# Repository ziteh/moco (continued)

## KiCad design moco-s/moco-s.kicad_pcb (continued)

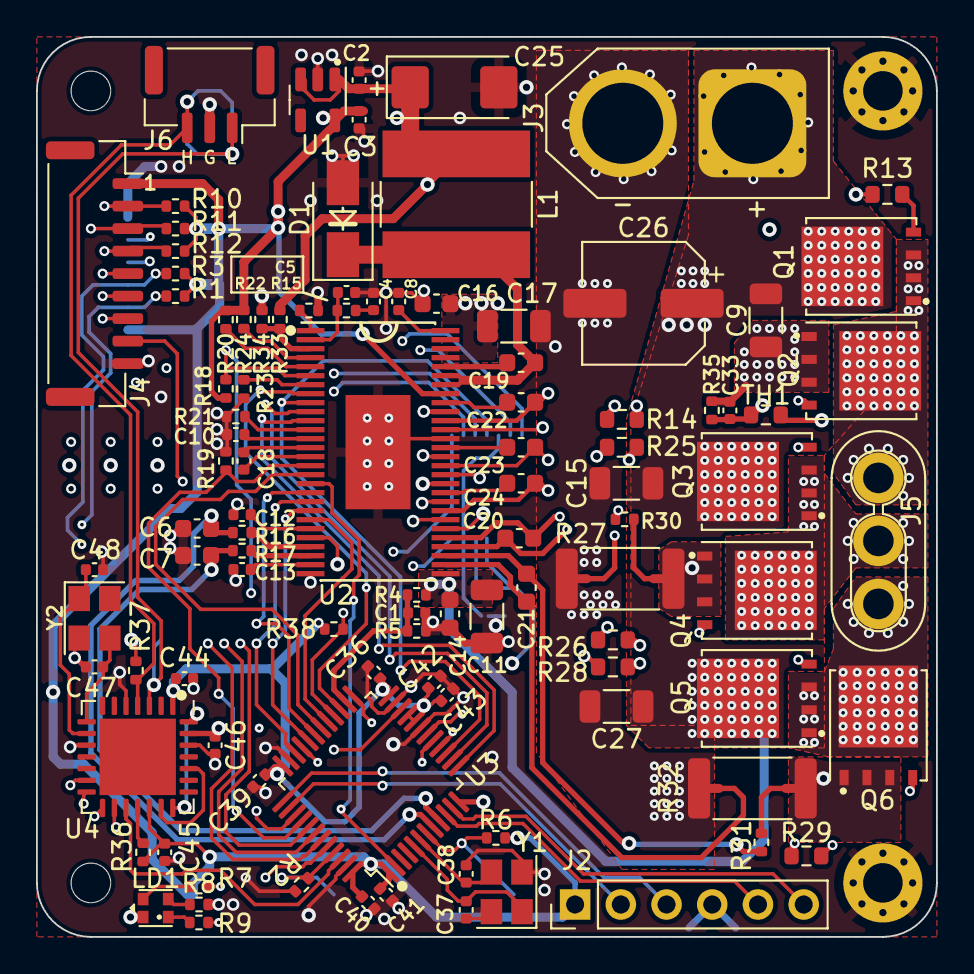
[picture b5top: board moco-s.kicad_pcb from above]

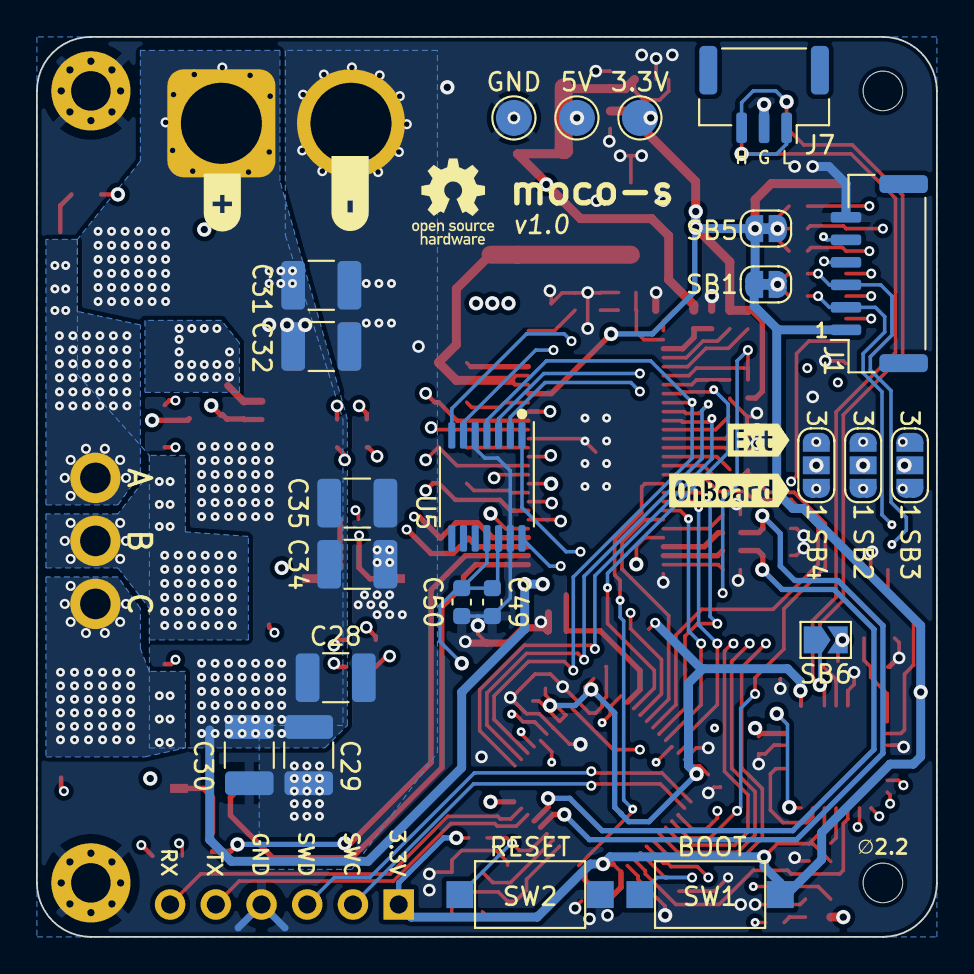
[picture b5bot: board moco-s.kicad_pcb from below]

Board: 4 copper layers, 50.0 x 50.0 mm, 135 parts (27 on the bottom side), 103 nets.

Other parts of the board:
J5: Conn_01x03; AMASS MR30PB-F
kibuzzard-638C8B7C: G***; kibuzzard-638C8B7C
kibuzzard-638C8BCF: G***; kibuzzard-638C8BCF
kibuzzard-638C8E4D: G***; kibuzzard-638C8E4D
kibuzzard-638C8E29: G***; kibuzzard-638C8E29

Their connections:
/Motor Driver/MOTOR_A: J5.1; also elsewhere on the board
/Motor Driver/MOTOR_B: J5.2; also elsewhere on the board
/Motor Driver/MOTOR_C: J5.3; also elsewhere on the board

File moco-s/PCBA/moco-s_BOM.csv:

Comment,Designator,Footprint,LCSC
82pF,C5,C_0402_1005Metric,C107011
47uF/50V,C26,CP_Elec_6.3x7.7,C108053
15nF,C8,C_0402_1005Metric,C114405
1k,"R19,R8",R_0402_1005Metric,C11702
NCP18XH103F03RB,TH1,R_0603_1608Metric,C13564
16MHz,Y2,Crystal_SMD_3225-4Pin_3.2x2.5mm,C13738
100nF/50V,"C14,C16,C19,C22,C23,C24",C_0603_1608Metric,C14663
100nF,"C36,C39,C40,C41,C42,C44,C45,C46",C_0402_1005Metric,C1525
22nF,C18,C_0402_1005Metric,C1532
12pF,"C37,C38",C_0402_1005Metric,C1547
10uF,C2,C_0402_1005Metric,C15525
22pF,"C47,C48",C_0402_1005Metric,C1555
2.2nF,"C20,C21,C6,C7",C_0603_1608Metric,C1604
MCP25625,U4,QFN-28-1EP_6x6mm_P0.65mm_EP4.25x4.25mm,C191253
2.2R,"R13,R14,R25,R26,R28,R29",R_0603_1608Metric,C22939
4.7uF,C3,C_0402_1005Metric,C23733
120R,"R30,R31,R37",R_0402_1005Metric,C25079
22R,"R16,R17",R_0402_1005Metric,C25092
330R,R9,R_0402_1005Metric,C25104
680R,"R5,R7",R_0402_1005Metric,C25130
10k,"R18,R2,R20,R24,R35,R36,R38,R4,R6",R_0402_1005Metric,C25744
18k,"R23,R33",R_0402_1005Metric,C25762
220k 1%,R22,R_0402_1005Metric,C25767
47k,R15,R_0402_1005Metric,C25792
3.3k,"R10,R11,R12,R21,R34",R_0402_1005Metric,C25890
4.7k,"R1,R3",R_0402_1005Metric,C25900
Conn_02x02_Top_Bottom,"J6,J7",JST_GH_SM03B-GHS-TB_1x03-1MP_P1.25mm_Horizontal,C2829252
Conn_01x06,J1,JST_GH_SM06B-GHS-TB_1x06-1MP_P1.25mm_Horizontal,C2829255
Conn_01x09,J4,JST_GH_SM09B-GHS-TB_1x09-1MP_P1.25mm_Horizontal,C2829258
4.7uF/50V,"C11,C17",C_1206_3216Metric,C29823
22uH/1.5A,L1,L_Bourns-SRN8040_8x8.15mm,C354640
LED_BAGR,LD1,RGB LED 1.6x1.6mm,C375569
0.5mΩ,"R27,R32",R_2512_6332Metric,C469426
AS5147,U5,TSSOP-14_4.4x5mm_P0.65mm,C481876
2.2uF/16V,"C10,C33",C_0402_1005Metric,C501836
2.2uF/50V,"C15,C27,C9",C_1206_3216Metric,C50254
SW_Push,"SW1,SW2",SW_SPST_CK_RS282G05A3,C520860
270pF,"C1,C4",C_0402_1005Metric,C524551
1uF,"C12,C13,C43",C_0402_1005Metric,C52923
STM32G431CBT6,U3,LQFP-48_7x7mm_P0.5mm,C529355
8MHz,Y1,Crystal_SMD_3225-4Pin_3.2x2.5mm,C57131
68uF,C25,CP_EIA-6032-28_Kemet-C,C7220
CSD18540Q5B,"Q1,Q2,Q3,Q4,Q5,Q6",TDSON-8-1,C86513
XC6220B331MR,U1,SOT-23-5,C86534
SS34,D1,D_SMA,C8678
Conn_01x02,J3,AMASS_XT60-M_1x02_P7.20mm_Vertical,C98733
DRV8301,U2,HTSSOP-56-1EP_6.1x14mm_P0.5mm_EP3.61x6.35mm,C98969
Debug,J2,PinHeader_1x06_P2.54mm_Vertical,
Conn_01x03,J5,AMASS MR30PB-F,
100nF,C50,C_0603_1608Metric,
22uF/50V,C29,C_1210_3225Metric_Pad1.33x2.70mm_HandSolder,
1uF,C49,C_0603_1608Metric,
22uF/50V,C30,C_1210_3225Metric_Pad1.33x2.70mm_HandSolder,
22uF/50V,C31,C_1210_3225Metric_Pad1.33x2.70mm_HandSolder,
22uF/50V,C32,C_1210_3225Metric_Pad1.33x2.70mm_HandSolder,
22uF/50V,C28,C_1210_3225Metric_Pad1.33x2.70mm_HandSolder,
22uF/50V,C35,C_1210_3225Metric_Pad1.33x2.70mm_HandSolder,
22uF/50V,C34,C_1210_3225Metric_Pad1.33x2.70mm_HandSolder,

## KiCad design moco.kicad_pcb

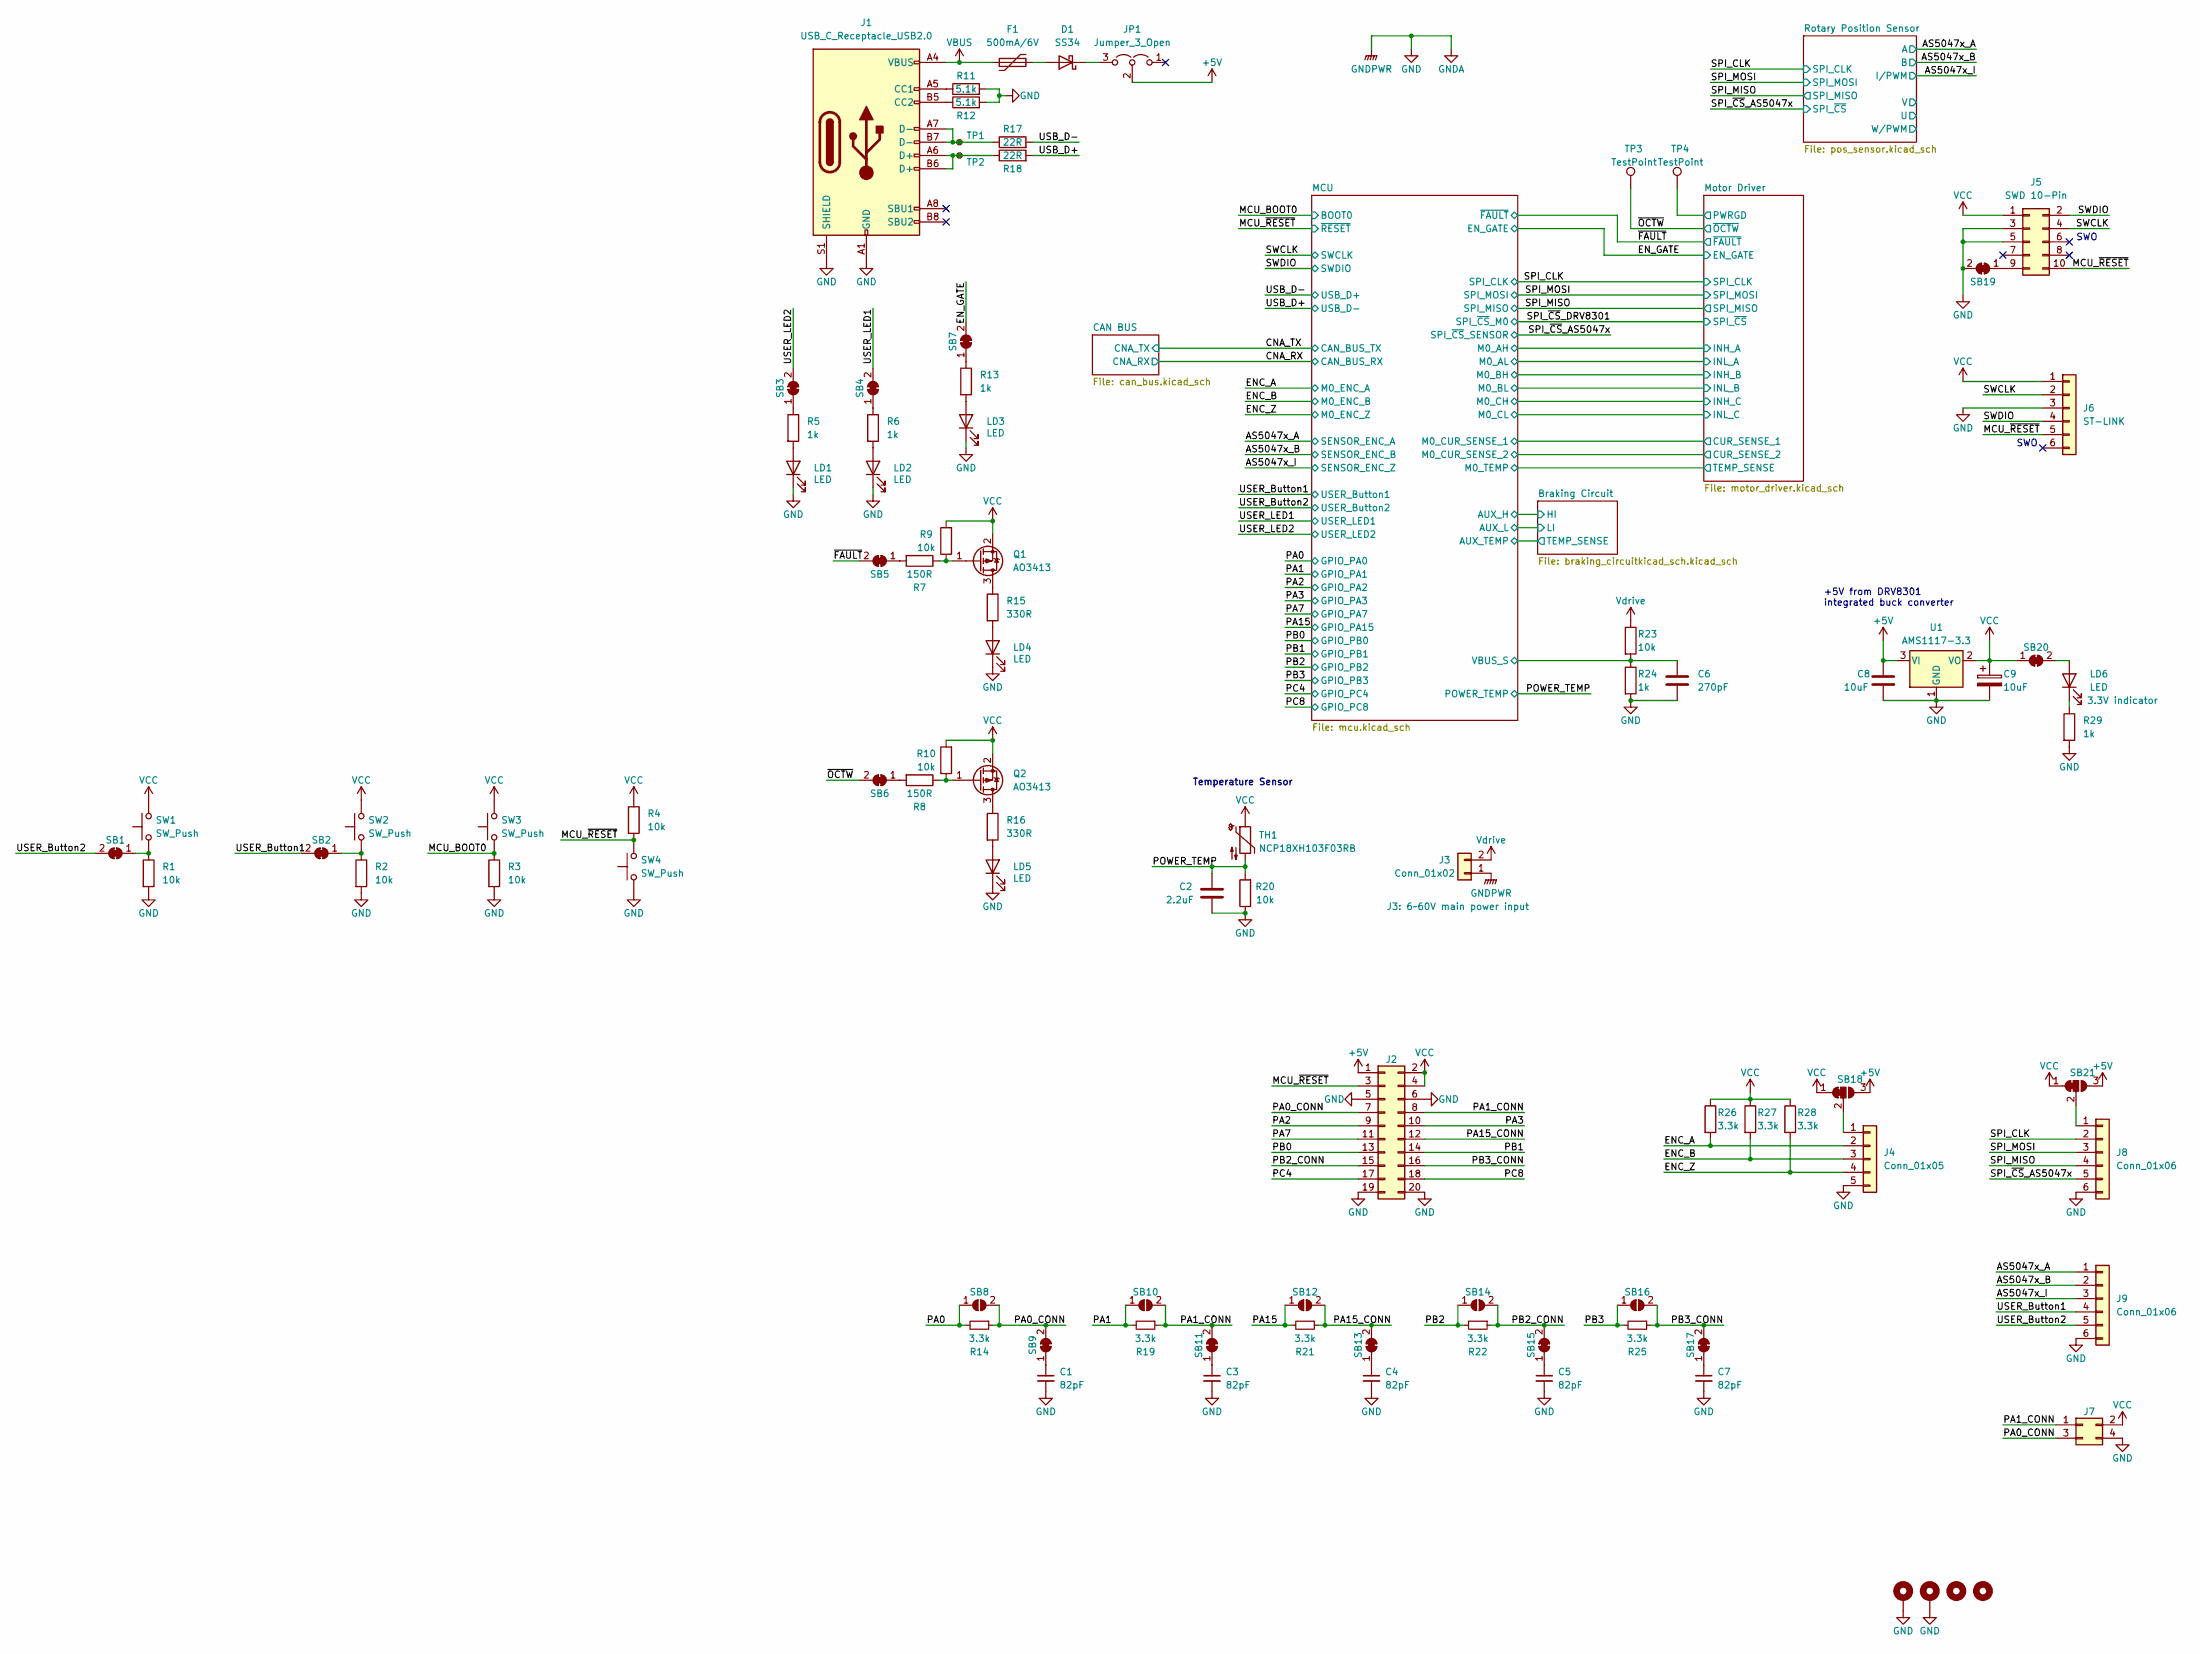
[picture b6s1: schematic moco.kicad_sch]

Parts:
C1, C3, C4, C5, C7: 82pF; C_0402_1005Metric; MFR.Part # CC0402JRNPO9BN820; JLCPCB Part # C107011
C2: 2.2uF; C_0402_1005Metric; MFR.Part # 0402X225K160NT; JLCPCB Part # C501836
C6: 270pF; C_0402_1005Metric; MFR.Part # GCM1555C1H271JA16D; JLCPCB Part # C524551
C8: 10uF; C_0402_1005Metric; MFR.Part # CL05A106MQ5NUNC; JLCPCB Part # C15525
C9: 10uF; CP_EIA-3216-18_Kemet-A; MFR.Part # TAJA106K016RNJ; JLCPCB Part # C7171
D1: SS34; D_SMA; MFR.Part # SS34; JLCPCB Part # C8678
F1: 500mA/6V; Fuse_0805_2012Metric; MFR.Part # SMD0805B050TF; JLCPCB Part # C269104
H1, H2: MountingHole_Pad; MountingHole_3.2mm_M3_Pad_Via
H3, H4: MountingHole; MountingHole_3.2mm_M3_ISO14580
J1: USB_C_Receptacle_USB2.0; USB_C_Receptacle_HRO_TYPE-C-31-M-12; MFR.Part # TYPE-C-31-M-12; JLCPCB Part # C165948
J2: Conn_02x10_Odd_Even; PinHeader_2x10_P2.54mm_Horizontal
J3: Conn_01x02; AMASS_XT60-F_1x02_P7.20mm_Vertical
J4: Conn_01x05; JST_PH_S5B-PH-SM4-TB_1x05-1MP_P2.00mm_Horizontal
J5: SWD 10-Pin; PinHeader_2x05_P1.27mm_Vertical_SMD
J6: ST-LINK; PinHeader_1x06_P2.54mm_Vertical
J7: Conn_02x02_Odd_Even; PinHeader_2x02_P2.54mm_Horizontal
J8, J9: Conn_01x06; JST_PH_S6B-PH-SM4-TB_1x06-1MP_P2.00mm_Horizontal
JP1: Jumper_3_Open; PinHeader_1x03_P2.54mm_Vertical
LD1, LD2, LD3, LD4, LD5, LD6: LED; LED_0603_1608Metric
Q1, Q2: AO3413; SOT-23; MFR.Part # AO3413A; JLCPCB Part # C545578
R1, R2, R3, R4, R9, R10, R20, R23: 10k; R_0402_1005Metric; MFR.Part # 0402WGF1002TCE; JLCPCB Part # C25744
R5, R6, R13, R24, R29: 1k; R_0402_1005Metric; MFR.Part # 0402WGF1001TCE; JLCPCB Part # C11702
R7, R8: 150R; R_0402_1005Metric; MFR.Part # 0402WGF1500TCE; JLCPCB Part # C25082
R11, R12: 5.1k; R_0402_1005Metric; MFR.Part # 0402WGF5101TCE; JLCPCB Part # C25905
R14, R19, R21, R22, R25, R26, R27, R28: 3.3k; R_0402_1005Metric; MFR.Part # 0402WGF3301TCE; JLCPCB Part # C25890
R15, R16: 330R; R_0402_1005Metric
R17, R18: 22R; R_0402_1005Metric; MFR.Part # 0402WGF220JTCE; JLCPCB Part # C25092
SB1, SB2, SB3, SB4, SB5, SB6, SB7, SB9, SB11, SB13, SB15, SB17, SB19, SB20: SolderJumper_2_Bridged; SolderJumper-2_P1.3mm_Bridged_RoundedPad1.0x1.5mm
SB8, SB10, SB12, SB14, SB16: SolderJumper_2_Open; SolderJumper-2_P1.3mm_Open_RoundedPad1.0x1.5mm
SB18, SB21: SolderJumper_3_Bridged12; SolderJumper-3_P1.3mm_Bridged12_RoundedPad1.0x1.5mm_NumberL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
SW1, SW2, SW3, SW4: SW_Push; SW_SPST_CK_RS282G05A3
TH1: NCP18XH103F03RB; R_0603_1608Metric; MFR.Part # NCP18XH103F03RB; JLCPCB Part # C13564
TP1, TP2: TestPoint_Small; TestPoint_Pad_D2.0mm
TP3, TP4: TestPoint; TestPoint_Pad_D2.0mm
U1: AMS1117-3.3; SOT-223-3_TabPin2; MFR.Part # AMS1117-3.3; JLCPCB Part # C6186

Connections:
+5V: C8.1, J2.1, JP1.2 (C), SB18.3 (B), SB21.3 (B), U1.3 (VI); also elsewhere on the board
/AS5047x_A: J9.1; also elsewhere on the board
/AS5047x_B: J9.2; also elsewhere on the board
/AS5047x_I: J9.3; also elsewhere on the board
/ENC_A: J4.2, R26.2; also elsewhere on the board
/ENC_B: J4.3, R27.2; also elsewhere on the board
/ENC_Z: J4.4, R28.2; also elsewhere on the board
/EN_GATE: SB7.2 (B); also elsewhere on the board
/MCU/VBUS_S: C6.1, R23.2, R24.1; also elsewhere on the board
/MCU_BOOT0: R3.1, SW3.1; also elsewhere on the board
/MCU_~RESET: J2.3, J5.10, J6.5, R4.2, SW4.2; also elsewhere on the board
/Motor Driver/PWRGD: TP4.1; also elsewhere on the board
/PA0: R14.2, SB8.1 (A); also elsewhere on the board
/PA0_CONN: J2.7, J7.3, R14.1, SB8.2 (B), SB9.2 (B)
/PA1: R19.2, SB10.1 (A); also elsewhere on the board
/PA1_CONN: J2.8, J7.1, R19.1, SB10.2 (B), SB11.2 (B)
/PA2: J2.9; also elsewhere on the board
/PA3: J2.10; also elsewhere on the board
/PA7: J2.11; also elsewhere on the board
/PA15: R21.2, SB12.1 (A); also elsewhere on the board
/PA15_CONN: J2.12, R21.1, SB12.2 (B), SB13.2 (B)
/PB0: J2.13; also elsewhere on the board
/PB1: J2.14; also elsewhere on the board
/PB2: R22.2, SB14.1 (A); also elsewhere on the board
/PB2_CONN: J2.15, R22.1, SB14.2 (B), SB15.2 (B)
/PB3: R25.2, SB16.1 (A); also elsewhere on the board
/PB3_CONN: J2.16, R25.1, SB16.2 (B), SB17.2 (B)
/PC4: J2.17; also elsewhere on the board
/PC8: J2.18; also elsewhere on the board
/POWER_TEMP: C2.1, R20.2, TH1.2; also elsewhere on the board
/SPI_CLK: J8.2; also elsewhere on the board
/SPI_MISO: J8.4; also elsewhere on the board
/SPI_MOSI: J8.3; also elsewhere on the board
/SPI_~CS_AS5047x: J8.5; also elsewhere on the board
/SWCLK: J5.4, J6.2; also elsewhere on the board
/SWDIO: J5.2, J6.4; also elsewhere on the board
/USB_D+: R18.2; also elsewhere on the board
/USB_D-: R17.2; also elsewhere on the board
/USER_Button1: J9.4, SB2.2 (B); also elsewhere on the board
/USER_Button2: J9.5, SB1.2 (B); also elsewhere on the board
/USER_LED1: SB4.2 (B); also elsewhere on the board
/USER_LED2: SB3.2 (B); also elsewhere on the board
/~FAULT: SB5.2 (B); also elsewhere on the board
/~OCTW: SB6.2 (B), TP3.1; also elsewhere on the board
unnamed: C1.1, SB9.1 (A)
unnamed: C3.1, SB11.1 (A)
unnamed: C4.1, SB13.1 (A)
unnamed: C5.1, SB15.1 (A)
unnamed: C7.1, SB17.1 (A)
unnamed: D1.1 (K), JP1.3 (B)
unnamed: D1.2 (A), F1.2
unnamed: J1.A5 (CC1), R11.1
unnamed: J1.A6 (D+), J1.B6 (D+), R18.1, TP2.1
unnamed: J1.A7 (D-), J1.B7 (D-), R17.1, TP1.1
unnamed: J1.B5 (CC2), R12.1
unnamed: J4.1, SB18.2 (C)
unnamed: J5.9, SB19.1 (A)
unnamed: J8.1, SB21.2 (C)
unnamed: LD1.2 (A), R5.2
unnamed: LD2.2 (A), R6.2
unnamed: LD3.2 (A), R13.2
unnamed: LD4.2 (A), R15.2
unnamed: LD5.2 (A), R16.2
unnamed: LD6.1 (K), R29.1
unnamed: LD6.2 (A), SB20.2 (B)
unnamed: Q1.1 (G), R7.1, R9.1
unnamed: Q1.3 (D), R15.1
unnamed: Q2.1 (G), R8.1, R10.1
unnamed: Q2.3 (D), R16.1
unnamed: R1.1, SB1.1 (A), SW1.1
unnamed: R2.1, SB2.1 (A), SW2.1
unnamed: R5.1, SB3.1 (A)
unnamed: R6.1, SB4.1 (A)
unnamed: R7.2, SB5.1 (A)
unnamed: R8.2, SB6.1 (A)
unnamed: R13.1, SB7.1 (A)
VBUS: F1.1, J1.A4 (VBUS), J1.A9 (VBUS), J1.B4 (VBUS), J1.B9 (VBUS)
VCC: C9.1, J2.2, J2.4, J5.1, J6.1, J7.2, Q1.2 (S), Q2.2 (S), R4.1, R9.2, R10.2, R26.1, R27.1, R28.1, SB18.1 (A), SB20.1 (A), SB21.1 (A), SW1.2, SW2.2, SW3.2, TH1.1, U1.2 (VO); also elsewhere on the board

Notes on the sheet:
Temperature Sensor
SWO
+5V from DRV8301 integrated buck converter

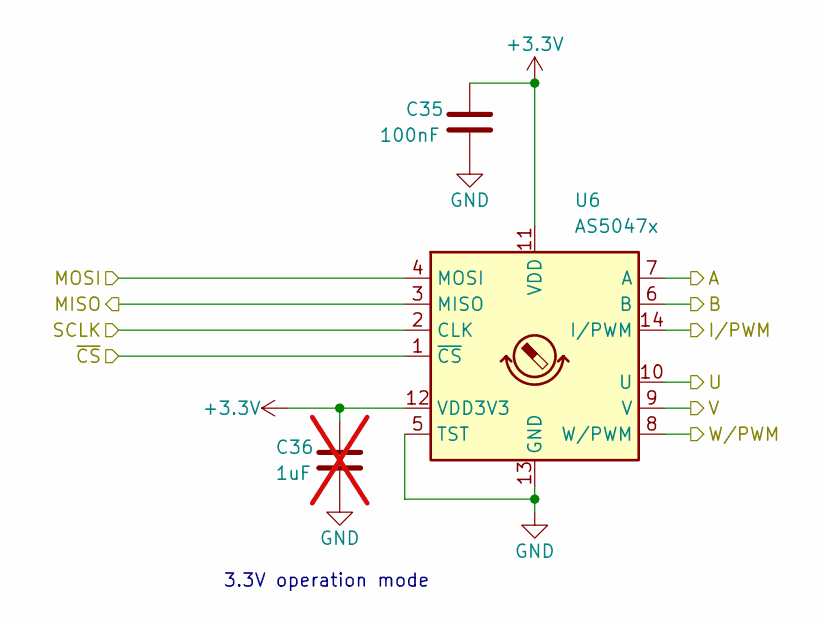
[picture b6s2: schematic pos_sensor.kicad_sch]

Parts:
C35: 100nF; C_0603_1608Metric_Pad1.08x0.95mm_HandSolder; MFR.Part # CL05B104KO5NNNC; JLCPCB Part # C1525
C36: 1uF; C_0603_1608Metric_Pad1.08x0.95mm_HandSolder; MFR.Part # CL05A105KA5NQNC; JLCPCB Part # C52923; not fitted
U6: AS5047x; TSSOP-14_4.4x5mm_P0.65mm; MFR.Part # AS5047P-ATSM; JLCPCB Part # C962063

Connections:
/Braking Circuit/HI: U6.2 (HI); also elsewhere on the board
/Braking Circuit/LI: U6.3 (LI); also elsewhere on the board
GATE_VDD: U6.1 (VDD); also elsewhere on the board
unnamed 103: U6.8 (HB); also elsewhere on the board
unnamed 104: U6.6 (HS); also elsewhere on the board
unnamed 146: U6.7 (HO); also elsewhere on the board

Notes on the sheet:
3.3V operation mode

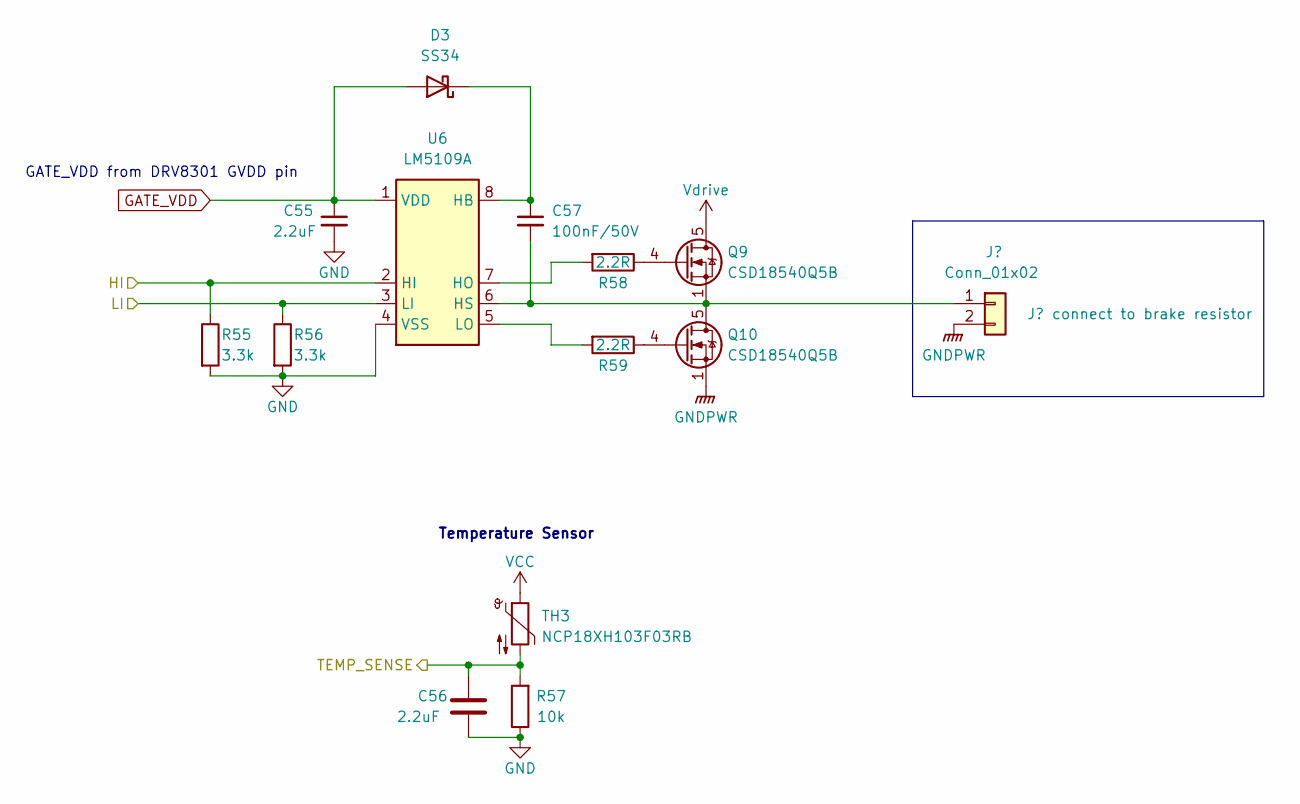
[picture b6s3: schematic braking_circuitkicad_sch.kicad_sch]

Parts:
C55, C56: 2.2uF; C_0402_1005Metric; MFR.Part # 0402X225K160NT; JLCPCB Part # C501836
C57: 100nF/50V; C_0603_1608Metric; MFR.Part # CC0603KRX7R9BB104; JLCPCB Part # C14663
D3: SS34; D_SMA; MFR.Part # SS34; JLCPCB Part # C8678
Q9, Q10: CSD18540Q5B; TDSON-8-1; MFR.Part # CSD18540Q5B; JLCPCB Part # C86513
R55, R56: 3.3k; R_0402_1005Metric; MFR.Part # 0402WGF3301TCE; JLCPCB Part # C25890
R57: 10k; R_0402_1005Metric; MFR.Part # 0402WGF1002TCE; JLCPCB Part # C25744
R58, R59: 2.2R; R_0603_1608Metric; MFR.Part # 0603WAJ022JT5E; JLCPCB Part # C25226
TH3: NCP18XH103F03RB; R_0603_1608Metric; MFR.Part # NCP18XH103F03RB; JLCPCB Part # C13564
U6: LM5109A; SOIC-8_3.9x4.9mm_P1.27mm; MFR.Part # LM5109AMAX/NOPB; JLCPCB Part # C129332

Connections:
/Braking Circuit/HI: R55.1, U6.2 (HI); also elsewhere on the board
/Braking Circuit/LI: R56.1, U6.3 (LI); also elsewhere on the board
/Braking Circuit/TEMP_SENSE: C56.1, R57.2, TH3.2; also elsewhere on the board
GATE_VDD: C55.1, D3.2 (A), U6.1 (VDD); also elsewhere on the board
unnamed: C57.1, D3.1 (K), U6.8 (HB)
unnamed 104: C57.2, Q9.1 (S), Q9.2 (S), Q9.3 (S), Q10.5 (D), U6.6 (HS); also elsewhere on the board
unnamed: Q9.4 (G), R58.1
unnamed: Q10.4 (G), R59.1
unnamed: R58.2, U6.7 (HO)
VCC: TH3.1; also elsewhere on the board

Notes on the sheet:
Temperature Sensor
GATE_VDD from DRV8301 GVDD pin

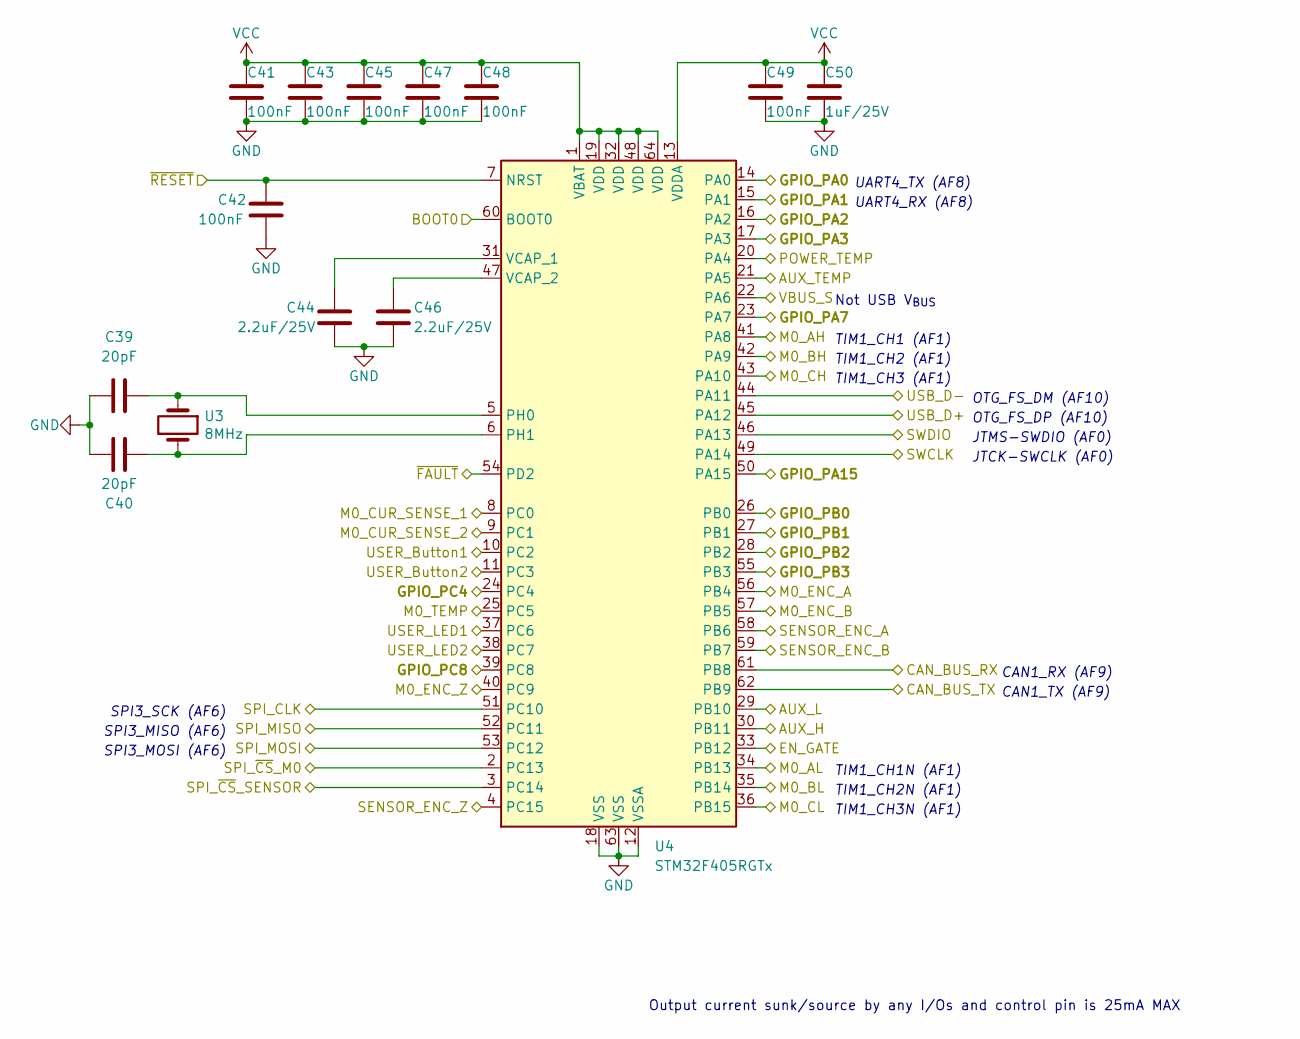
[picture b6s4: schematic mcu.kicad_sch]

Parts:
C39, C40: 20pF; C_0402_1005Metric
C41, C42, C43, C45, C47, C48, C49: 100nF; C_0402_1005Metric; MFR.Part # CL05B104KO5NNNC; JLCPCB Part # C1525
C44, C46: 2.2uF/25V; C_0402_1005Metric
C50: 1uF/25V; C_0402_1005Metric
U3: 8MHz; Crystal_SMD_5032-2Pin_5.0x3.2mm; MFR.Part # X50328MSB2GI; JLCPCB Part # C115962
U4: STM32F405RGTx; LQFP-64_10x10mm_P0.5mm; MFR.Part # STM32F405RGT6; JLCPCB Part # C15742

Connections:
/AS5047x_A: U4.58 (PB6); also elsewhere on the board
/AS5047x_B: U4.59 (PB7); also elsewhere on the board
/AS5047x_I: U4.4 (PC15); also elsewhere on the board
/Braking Circuit/HI: U4.30 (PB11); also elsewhere on the board
/Braking Circuit/LI: U4.29 (PB10); also elsewhere on the board
/Braking Circuit/TEMP_SENSE: U4.21 (PA5); also elsewhere on the board
/CNA_RX: U4.61 (PB8); also elsewhere on the board
/CNA_TX: U4.62 (PB9); also elsewhere on the board
/ENC_A: U4.56 (PB4); also elsewhere on the board
/ENC_B: U4.57 (PB5); also elsewhere on the board
/ENC_Z: U4.40 (PC9); also elsewhere on the board
/EN_GATE: U4.33 (PB12); also elsewhere on the board
/MCU/M0_AH: U4.41 (PA8); also elsewhere on the board
/MCU/M0_AL: U4.34 (PB13); also elsewhere on the board
/MCU/M0_BH: U4.42 (PA9); also elsewhere on the board
/MCU/M0_BL: U4.35 (PB14); also elsewhere on the board
/MCU/M0_CH: U4.43 (PA10); also elsewhere on the board
/MCU/M0_CL: U4.36 (PB15); also elsewhere on the board
/MCU/M0_CUR_SENSE_1: U4.8 (PC0); also elsewhere on the board
/MCU/M0_CUR_SENSE_2: U4.9 (PC1); also elsewhere on the board
/MCU/VBUS_S: U4.22 (PA6); also elsewhere on the board
/MCU_BOOT0: U4.60 (BOOT0); also elsewhere on the board
/MCU_~RESET: C42.1, U4.7 (NRST); also elsewhere on the board
/PA0: U4.14 (PA0); also elsewhere on the board
/PA1: U4.15 (PA1); also elsewhere on the board
/PA2: U4.16 (PA2); also elsewhere on the board
/PA3: U4.17 (PA3); also elsewhere on the board
/PA7: U4.23 (PA7); also elsewhere on the board
/PA15: U4.50 (PA15); also elsewhere on the board
/PB0: U4.26 (PB0); also elsewhere on the board
/PB1: U4.27 (PB1); also elsewhere on the board
/PB2: U4.28 (PB2); also elsewhere on the board
/PB3: U4.55 (PB3); also elsewhere on the board
/PC4: U4.24 (PC4); also elsewhere on the board
/PC8: U4.39 (PC8); also elsewhere on the board
/POWER_TEMP: U4.20 (PA4); also elsewhere on the board
/SPI_CLK: U4.51 (PC10); also elsewhere on the board
/SPI_MISO: U4.52 (PC11); also elsewhere on the board
/SPI_MOSI: U4.53 (PC12); also elsewhere on the board
/SPI_~CS_AS5047x: U4.3 (PC14); also elsewhere on the board
/SPI_~CS_DRV8301: U4.2 (PC13); also elsewhere on the board
/SWCLK: U4.49 (PA14); also elsewhere on the board
/SWDIO: U4.46 (PA13); also elsewhere on the board
/USB_D+: U4.44 (PA11); also elsewhere on the board
/USB_D-: U4.45 (PA12); also elsewhere on the board
/USER_Button1: U4.10 (PC2); also elsewhere on the board
/USER_Button2: U4.11 (PC3); also elsewhere on the board
/USER_LED1: U4.37 (PC6); also elsewhere on the board
/USER_LED2: U4.38 (PC7); also elsewhere on the board
/~FAULT: U4.54 (PD2); also elsewhere on the board
unnamed: C39.2, U3.1, U4.5 (PH0)
unnamed: C40.2, U3.2, U4.6 (PH1)
unnamed: C44.1, U4.31 (VCAP_1)
unnamed: C46.1, U4.47 (VCAP_2)
VCC: C41.1, C43.1, C45.1, C47.1, C48.1, C49.1, C50.1, U4.1 (VBAT), U4.13 (VDDA), U4.19 (VDD), U4.32 (VDD), U4.48 (VDD), U4.64 (VDD); also elsewhere on the board

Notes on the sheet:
UART4_TX (AF8)
TIM1_CH2 (AF1)
TIM1_CH1 (AF1)
Output current sunk/source by any I/Os and control pin is 25mA MAX
TIM1_CH1N (AF1)
TIM1_CH2N (AF1)
TIM1_CH3 (AF1)
TIM1_CH3N (AF1)
SPI3_SCK (AF6)
JTMS-SWDIO (AF0)
SPI3_MOSI (AF6)
SPI3_MISO (AF6)
OTG_FS_DM (AF10)
CAN1_RX (AF9)
JTCK-SWCLK (AF0)
Not USB V_{BUS}
OTG_FS_DP (AF10)
CAN1_TX (AF9)
UART4_RX (AF8)

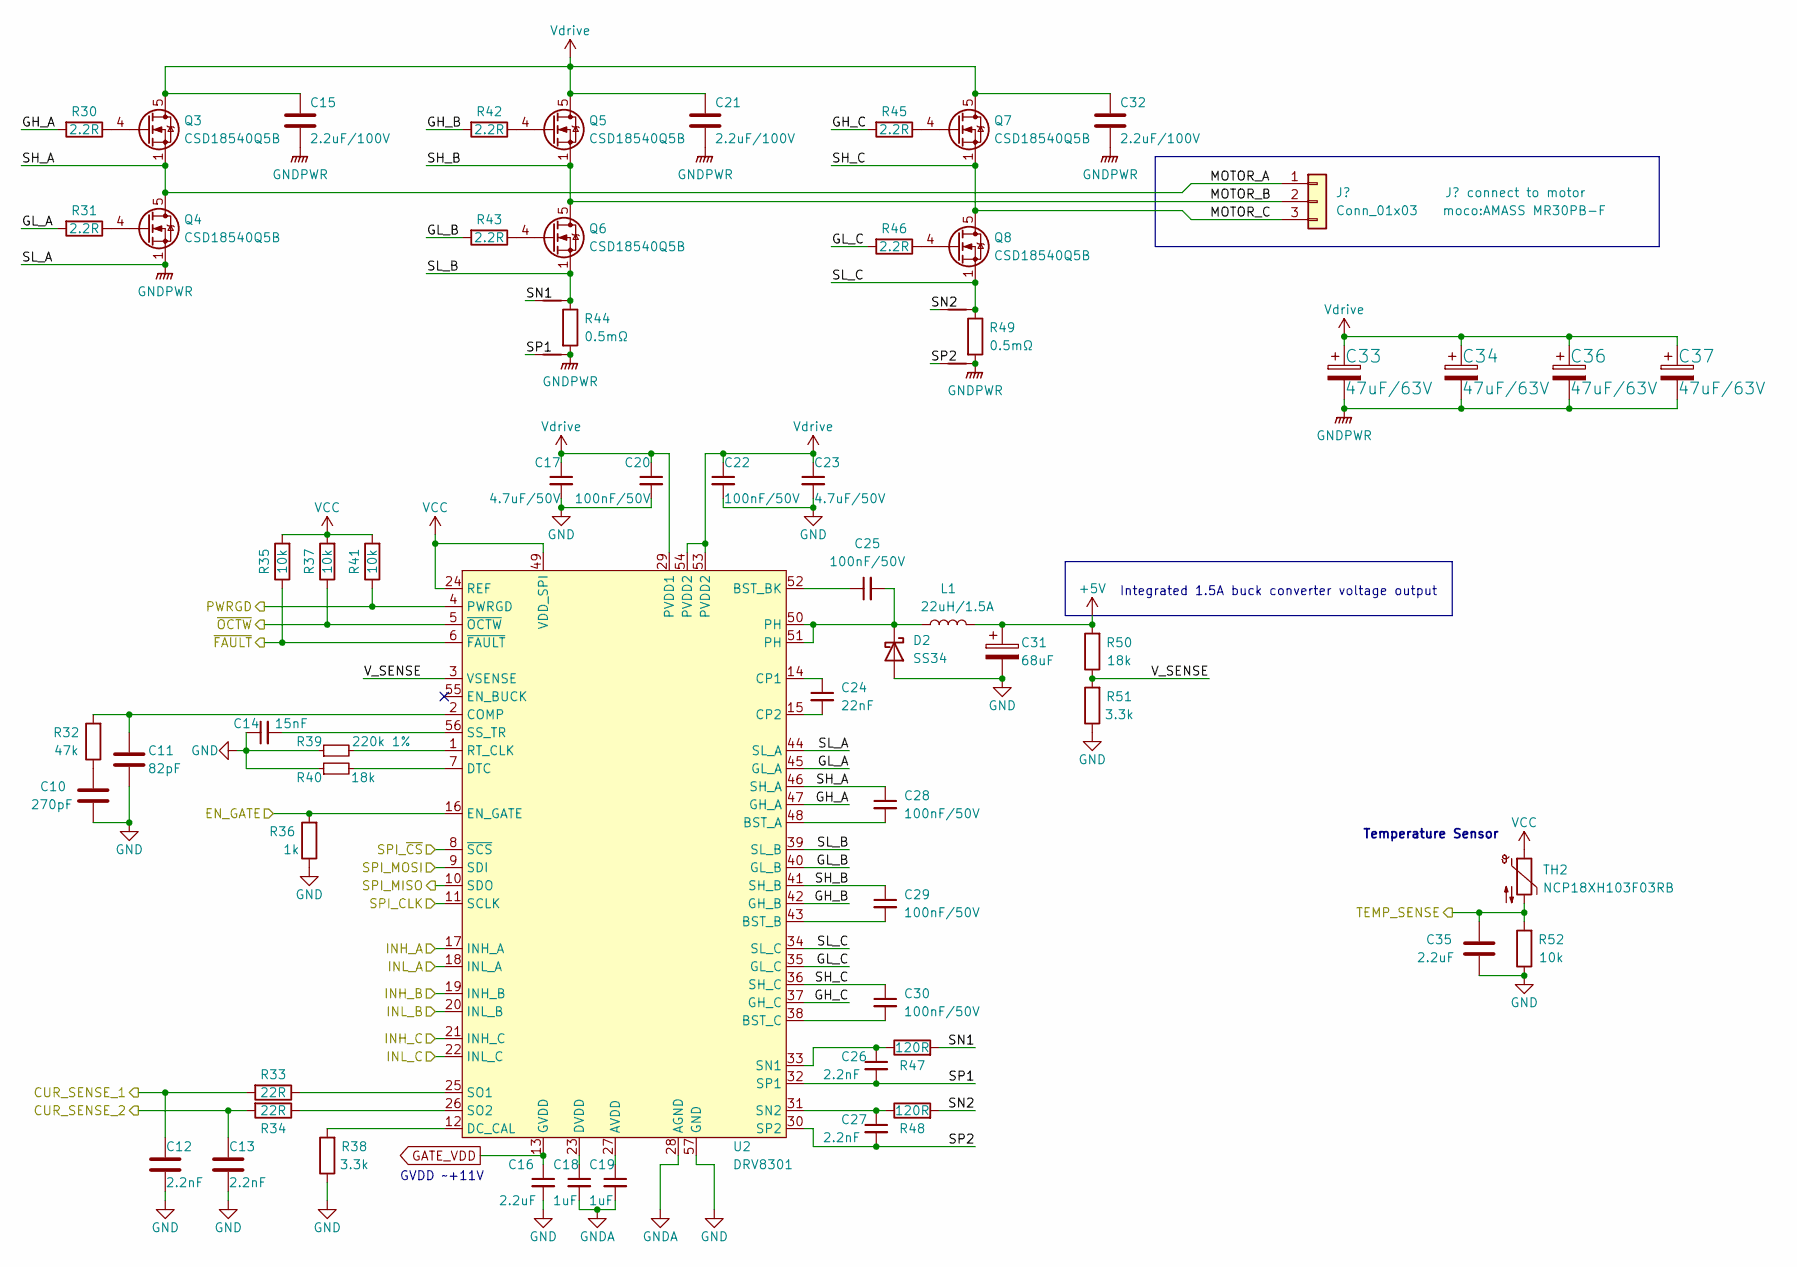
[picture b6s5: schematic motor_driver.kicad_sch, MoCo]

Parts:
C10: 270pF; C_0402_1005Metric; MFR.Part # GCM1555C1H271JA16D; JLCPCB Part # C524551
C11: 82pF; C_0402_1005Metric; MFR.Part # CC0402JRNPO9BN820; JLCPCB Part # C107011
C12, C13, C26, C27: 2.2nF; C_0603_1608Metric; MFR.Part # 0603B222K500NT; JLCPCB Part # C1604
C14: 15nF; C_0402_1005Metric
C15, C21, C32: 2.2uF/100V; C_1206_3216Metric; MFR.Part # HMK316AC7225KLHTE; JLCPCB Part # C650969
C16, C35: 2.2uF; C_0402_1005Metric; MFR.Part # 0402X225K160NT; JLCPCB Part # C501836
C17, C23: 4.7uF/50V; C_1206_3216Metric; MFR.Part # 1206B475K500NT; JLCPCB Part # C29823
C18, C19: 1uF; C_0402_1005Metric; MFR.Part # CL05A105KA5NQNC; JLCPCB Part # C52923
C20, C22, C25, C28, C29, C30: 100nF/50V; C_0603_1608Metric; MFR.Part # CC0603KRX7R9BB104; JLCPCB Part # C14663
C24: 22nF; C_0402_1005Metric; MFR.Part # 0402B223K500NT; JLCPCB Part # C1532
C31: 68uF; CP_EIA-7343-31_Kemet-D; MFR.Part # TAJD686K016RNJ; JLCPCB Part # C11382
C33, C34, C36, C37: 47uF/63V; CP_Elec_8x10; MFR.Part # RVT1J470M0810; JLCPCB Part # C72524
D2: SS34; D_SMA; MFR.Part # SS34; JLCPCB Part # C8678
L1: 22uH/1.5A; L_Bourns-SRN8040_8x8.15mm; MFR.Part # CKCS8040-22uH/M; JLCPCB Part # C354640
NT5, NT6, NT8, NT9: NetTie_2; NetTie-2_SMD_Pad0.5mm
Q3, Q4, Q5, Q6, Q7, Q8: CSD18540Q5B; TDSON-8-1; MFR.Part # CSD18540Q5B; JLCPCB Part # C86513
R30, R31, R42, R43, R45, R46: 2.2R; R_0603_1608Metric; MFR.Part # 0603WAJ022JT5E; JLCPCB Part # C25226
R32: 47k; R_0402_1005Metric; MFR.Part # 0402WGF4702TCE; JLCPCB Part # C25792
R33, R34: 22R; R_0402_1005Metric; MFR.Part # 0402WGF220JTCE; JLCPCB Part # C25092
R35, R37, R41, R52: 10k; R_0402_1005Metric; MFR.Part # 0402WGF1002TCE; JLCPCB Part # C25744
R36: 1k; R_0402_1005Metric; MFR.Part # 0402WGF1001TCE; JLCPCB Part # C11702
R38, R51: 3.3k; R_0402_1005Metric; MFR.Part # 0402WGF3301TCE; JLCPCB Part # C25890
R39: 220k 1%; R_0402_1005Metric
R40, R50: 18k; R_0402_1005Metric; MFR.Part # 0402WGF1802TCE; JLCPCB Part # C25762
R44, R49: 0.5mΩ; R_2512_6332Metric
R47, R48: 120R; R_0402_1005Metric; MFR.Part # 0402WGF1200TCE; JLCPCB Part # C25079
TH2: NCP18XH103F03RB; R_0603_1608Metric; MFR.Part # NCP18XH103F03RB; JLCPCB Part # C13564
U2: DRV8301; HTSSOP-56-1EP_6.1x14mm_P0.5mm_EP3.61x6.35mm; MFR.Part # DRV8301DCAR; JLCPCB Part # C98969

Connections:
+5V: C31.1, L1.2, R50.2; also elsewhere on the board
/EN_GATE: R36.2, U2.16 (EN_GATE); also elsewhere on the board
/MCU/M0_AH: U2.17 (INH_A); also elsewhere on the board
/MCU/M0_AL: U2.18 (INL_A); also elsewhere on the board
/MCU/M0_BH: U2.19 (INH_B); also elsewhere on the board
/MCU/M0_BL: U2.20 (INL_B); also elsewhere on the board
/MCU/M0_CH: U2.21 (INH_C); also elsewhere on the board
/MCU/M0_CL: U2.22 (INL_C); also elsewhere on the board
/MCU/M0_CUR_SENSE_1: C12.1, R33.2; also elsewhere on the board
/MCU/M0_CUR_SENSE_2: C13.1, R34.2; also elsewhere on the board
/Motor Driver/GH_A: R30.2, U2.47 (GH_A)
/Motor Driver/GH_B: R42.2, U2.42 (GH_B)
/Motor Driver/GH_C: R45.2, U2.37 (GH_C)
/Motor Driver/GL_A: R31.2, U2.45 (GL_A)
/Motor Driver/GL_B: R43.2, U2.40 (GL_B)
/Motor Driver/GL_C: R46.2, U2.35 (GL_C)
/Motor Driver/PWRGD: R41.1, U2.4 (PWRGD); also elsewhere on the board
/Motor Driver/SH_A: C28.1, Q3.1 (S), Q3.2 (S), Q3.3 (S), Q4.5 (D), U2.46 (SH_A); also elsewhere on the board
/Motor Driver/SH_B: C29.1, Q5.1 (S), Q5.2 (S), Q5.3 (S), Q6.5 (D), U2.41 (SH_B); also elsewhere on the board
/Motor Driver/SH_C: C30.1, Q7.1 (S), Q7.2 (S), Q7.3 (S), Q8.5 (D), U2.36 (SH_C); also elsewhere on the board
/Motor Driver/SL_B: NT5.2, Q6.1 (S), Q6.2 (S), Q6.3 (S), R44.1, U2.39 (SL_B)
/Motor Driver/SL_C: NT8.2, Q8.1 (S), Q8.2 (S), Q8.3 (S), R49.1, U2.34 (SL_C)
/Motor Driver/SN1: NT5.1, R47.2
/Motor Driver/SN2: NT8.1, R48.2
/Motor Driver/SP1: C26.2, NT6.1, U2.32 (SP1)
/Motor Driver/SP2: C27.2, NT9.1, U2.30 (SP2)
/Motor Driver/V_SENSE: R50.1, R51.2, U2.3 (VSENSE)
/SPI_CLK: U2.11 (SCLK); also elsewhere on the board
/SPI_MISO: U2.10 (SDO); also elsewhere on the board
/SPI_MOSI: U2.9 (SDI); also elsewhere on the board
/SPI_~CS_DRV8301: U2.8 (~SCS); also elsewhere on the board
/~FAULT: R35.1, U2.6 (~FAULT); also elsewhere on the board
/~OCTW: R37.1, U2.5 (~OCTW); also elsewhere on the board
GATE_VDD: C16.1, U2.13 (GVDD); also elsewhere on the board
unnamed: C10.1, R32.1
unnamed: C11.1, R32.2, U2.2 (COMP)
unnamed: C14.2, U2.56 (SS_TR)
unnamed: C18.1, U2.23 (DVDD)
unnamed: C19.1, U2.27 (AVDD)
unnamed: C24.1, U2.14 (CP1)
unnamed: C24.2, U2.15 (CP2)
unnamed: C25.1, U2.52 (BST_BK)
unnamed: C25.2, D2.1 (K), L1.1, U2.50 (PH), U2.51 (PH)
unnamed: C26.1, R47.1, U2.33 (SN1)
unnamed: C27.1, R48.1, U2.31 (SN2)
unnamed: C28.2, U2.48 (BST_A)
unnamed: C29.2, U2.43 (BST_B)
unnamed: C30.2, U2.38 (BST_C)
unnamed: Q3.4 (G), R30.1
unnamed: Q4.4 (G), R31.1
unnamed: Q5.4 (G), R42.1
unnamed: Q6.4 (G), R43.1
unnamed: Q7.4 (G), R45.1
unnamed: Q8.4 (G), R46.1
unnamed: R33.1, U2.25 (SO1)
unnamed: R34.1, U2.26 (SO2)
unnamed: R38.2, U2.12 (DC_CAL)
unnamed: R39.2, U2.1 (RT_CLK)
unnamed: R40.2, U2.7 (DTC)
VCC: R35.2, R37.2, R41.2, TH2.1, U2.24 (REF), U2.49 (VDD_SPI); also elsewhere on the board

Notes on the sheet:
Integrated 1.5A buck converter voltage output
Temperature Sensor
GVDD ~+11V
